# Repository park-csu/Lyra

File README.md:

# Lyra

## 40%, Ortholinear, Split keyboard with knob

### Photos

[Parts List and Build Guide(WIP)](build_guide.md)

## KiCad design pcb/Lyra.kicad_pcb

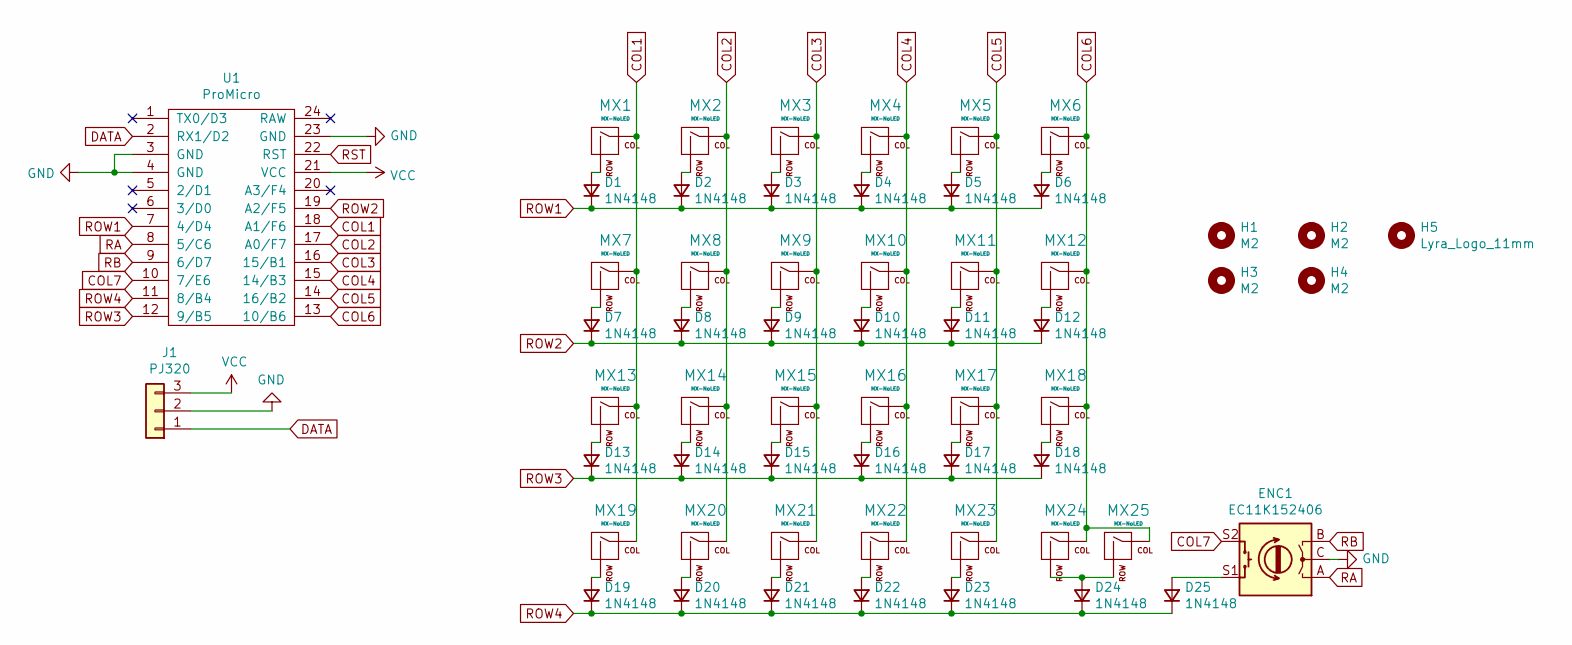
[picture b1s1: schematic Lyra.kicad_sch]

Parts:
D1, D2, D3, D4, D5, D6, D7, D8, D9, D10, D11, D12, D13, D14, D15, D16, D17, D18, D19, D20, D21, D22, D23, D24, D25: 1N4148; D_DO-35_SOD27_P7.62mm_Horizontal_With_SOD-123_2Sided
ENC1: EC11K152406; RotaryEncoder_Alps_EC11K-Switch_Vertical_H20mm_TwoSided
H1, H2, H3, H4: M2; MountingHole_2.2mm_M2
H5: Lyra_Logo_11mm; Lyra_Icon_11mm
J1: PJ320; PJ320-Reversible
MX1, MX2, MX3, MX4, MX5, MX6, MX7, MX8, MX9, MX10, MX11, MX12, MX13, MX14, MX15, MX16, MX17, MX18, MX19, MX20, MX21, MX22, MX23, MX24: MX-NoLED; MXOnly-1U-NoLED-Reversible
MX25: MX-NoLED; MXOnly-2U-ReversedStabilizers-NoLED-Reversible
U1: ProMicro; ProMicro_TwoSided

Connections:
COL1: MX1.1 (COL), MX7.1 (COL), MX13.1 (COL), MX19.1 (COL), U1.18 (A1/F6)
COL2: MX2.1 (COL), MX8.1 (COL), MX14.1 (COL), MX20.1 (COL), U1.17 (A0/F7)
COL3: MX3.1 (COL), MX9.1 (COL), MX15.1 (COL), MX21.1 (COL), U1.16 (15/B1)
COL4: MX4.1 (COL), MX10.1 (COL), MX16.1 (COL), MX22.1 (COL), U1.15 (14/B3)
COL5: MX5.1 (COL), MX11.1 (COL), MX17.1 (COL), MX23.1 (COL), U1.14 (16/B2)
COL6: MX6.1 (COL), MX12.1 (COL), MX18.1 (COL), MX24.1 (COL), MX25.1 (COL), U1.13 (10/B6)
COL7: ENC1.S2, U1.10 (7/E6)
DATA: J1.1, U1.2 (RX1/D2)
GND: ENC1.C, J1.2, U1.3 (GND), U1.4 (GND), U1.23 (GND)
unnamed: D1.2 (A), MX1.2 (ROW)
unnamed: D2.2 (A), MX2.2 (ROW)
unnamed: D3.2 (A), MX3.2 (ROW)
unnamed: D4.2 (A), MX4.2 (ROW)
unnamed: D5.2 (A), MX5.2 (ROW)
unnamed: D6.2 (A), MX6.2 (ROW)
unnamed: D7.2 (A), MX7.2 (ROW)
unnamed: D8.2 (A), MX8.2 (ROW)
unnamed: D9.2 (A), MX9.2 (ROW)
unnamed: D10.2 (A), MX10.2 (ROW)
unnamed: D11.2 (A), MX11.2 (ROW)
unnamed: D12.2 (A), MX12.2 (ROW)
unnamed: D13.2 (A), MX13.2 (ROW)
unnamed: D14.2 (A), MX14.2 (ROW)
unnamed: D15.2 (A), MX15.2 (ROW)
unnamed: D16.2 (A), MX16.2 (ROW)
unnamed: D17.2 (A), MX17.2 (ROW)
unnamed: D18.2 (A), MX18.2 (ROW)
unnamed: D19.2 (A), MX19.2 (ROW)
unnamed: D20.2 (A), MX20.2 (ROW)
unnamed: D21.2 (A), MX21.2 (ROW)
unnamed: D22.2 (A), MX22.2 (ROW)
unnamed: D23.2 (A), MX23.2 (ROW)
unnamed: D24.2 (A), MX24.2 (ROW), MX25.2 (ROW)
unnamed: D25.2 (A), ENC1.S1
RA: ENC1.A, U1.8 (5/C6)
RB: ENC1.B, U1.9 (6/D7)
ROW1: D1.1 (K), D2.1 (K), D3.1 (K), D4.1 (K), D5.1 (K), D6.1 (K), U1.7 (4/D4)
ROW2: D7.1 (K), D8.1 (K), D9.1 (K), D10.1 (K), D11.1 (K), D12.1 (K), U1.19 (A2/F5)
ROW3: D13.1 (K), D14.1 (K), D15.1 (K), D16.1 (K), D17.1 (K), D18.1 (K), U1.12 (9/B5)
ROW4: D19.1 (K), D20.1 (K), D21.1 (K), D22.1 (K), D23.1 (K), D24.1 (K), D25.1 (K), U1.11 (8/B4)
RST: U1.22 (RST)
VCC: J1.3, U1.21 (VCC)

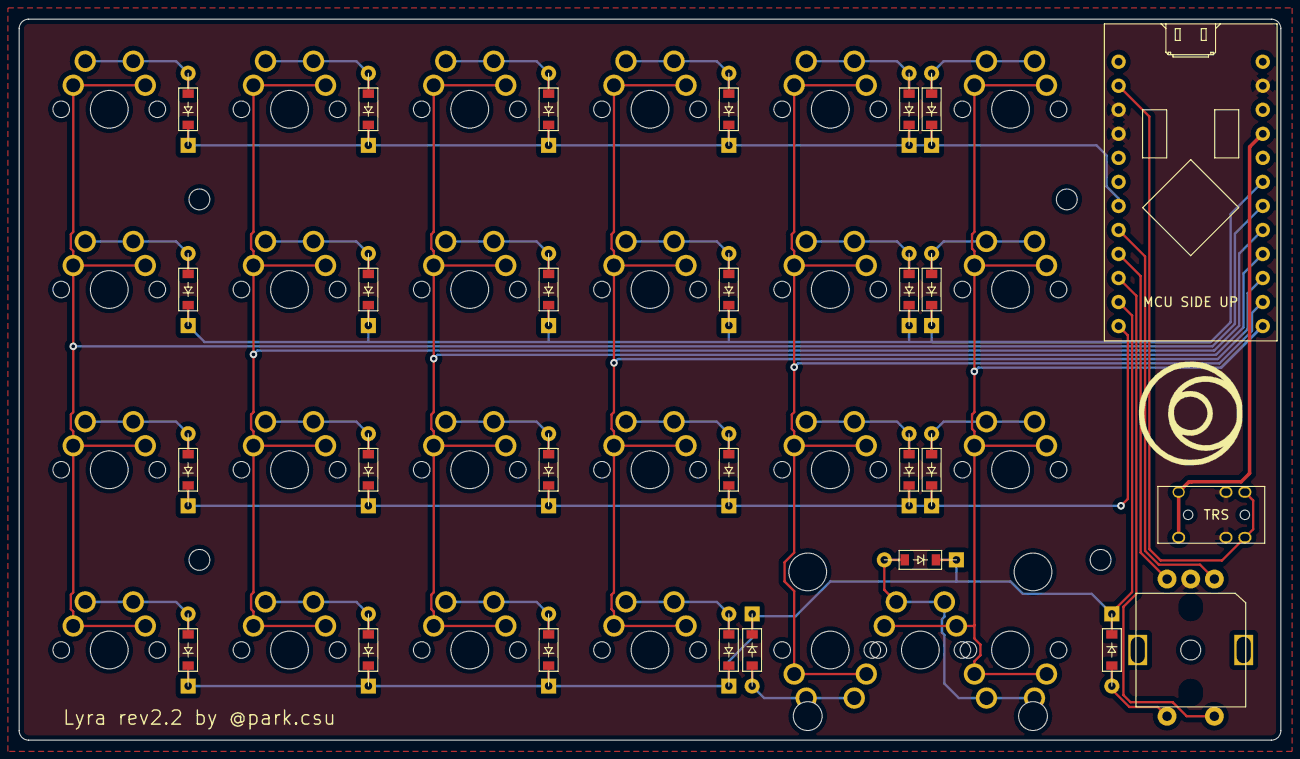
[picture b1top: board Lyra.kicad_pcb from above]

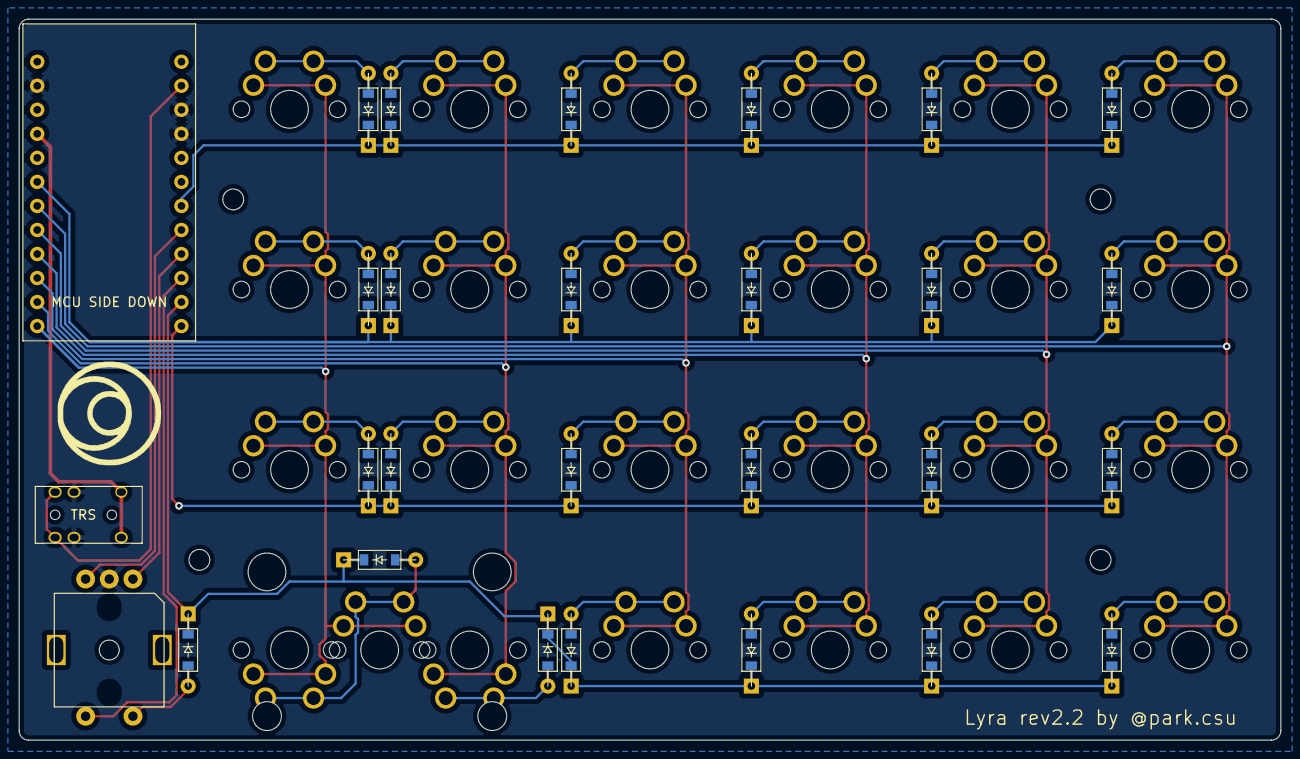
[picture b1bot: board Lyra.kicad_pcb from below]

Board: 2 copper layers, 133.3 x 76.2 mm, 58 parts (25 on the bottom side), 41 nets.

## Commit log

2021-07-31 rev2 release
2021-07-31 rev2.0 release
2021-07-31 Added README.md(WIP)
2021-07-31 Fixed submodule
2021-07-31 Removed submodule
2021-07-31 Added footprints again
2021-08-05 Plated hole
2021-08-11 rev2.0 -> rev2.1
2021-08-13 rev2.1->rev2.2(WIP)
2021-08-13 Submodule added
2021-08-13 Forgot to add production files
2021-08-13 applied .gitignore to existing files
2021-08-14 Added screw hole for the plate
2021-08-14 Consistent Line Thickness
2021-08-15 Project rename
2021-08-15 Added production file
2021-08-16 Updated production file
2021-08-16 Parts list added
2021-08-16 Added pcb render
2021-08-18 Fixed plate grid origin, rewired column bus
2021-08-18 Add SOD-123 diode support
2021-08-19 Fixed footprint
2021-08-19 Parts list update
2021-08-24 Fixed number of pins
2021-11-12 Updated files to newest revision
2021-11-12 Fixed file path
2021-11-12 Fixed pj320 footprint and library path
